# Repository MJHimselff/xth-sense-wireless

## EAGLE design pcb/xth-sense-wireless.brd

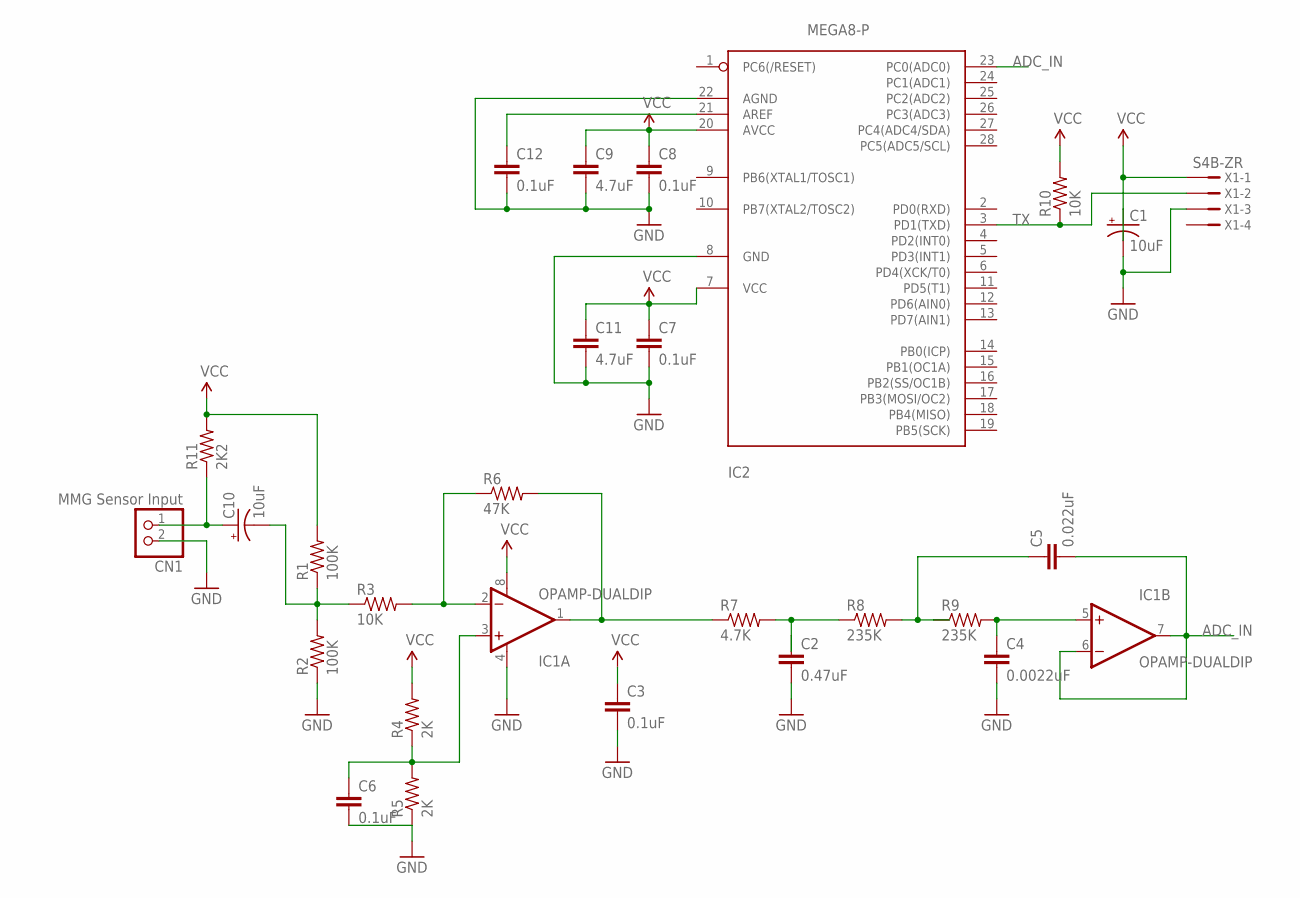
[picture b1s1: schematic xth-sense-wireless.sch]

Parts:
C1, C10: 10uF; CPOL-RADIAL-10UF-25V
C2: 0.47uF; CAP-PTH-SMALL
C3, C6, C7, C8, C12: 0.1uF; CAP-PTH-SMALL
C4: 0.0022uF; CAP-PTH-SMALL
C5: 0.022uF; CAP-PTH-SMALL
C9, C11: 4.7uF; CAP-PTH-SMALL
CN1: MMG Sensor Input; JST-PH-2-THM-RA
IC1: OPAMP-DUALDIP; DIP08
IC2: MEGA8-P; DIL28-3
R1, R2: 100K; AXIAL-0.3
R3, R10: 10K; AXIAL-0.3
R4, R5: 2K; AXIAL-0.3
R6: 47K; AXIAL-0.3
R7: 4.7K; AXIAL-0.3
R8, R9: 235K; AXIAL-0.3
R11: 2K2; AXIAL-0.3
X1: S4B-ZR

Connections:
ADC_IN: C5.2, IC1.6 (-IN), IC1.7 (OUT), IC2.23 (PC0(ADC0))
GND: C1.2 (-), C2.2, C3.2, C4.2, C6.2, C7.2, C8.2, C9.2, C11.2, C12.2, CN1.2 (1), IC1.4 (V-), IC2.8 (GND), IC2.22 (AGND), R2.P$1 (1), R5.P$1 (1), X1.3
unnamed: C10.2 (-), R1.P$1 (1), R2.P$2 (2), R3.P$1 (1)
unnamed: IC1.1 (OUT), R6.P$2 (2), R7.P$1 (1)
unnamed: IC1.2 (-IN), R3.P$2 (2), R6.P$1 (1)
unnamed: C2.1, R7.P$2 (2), R8.P$1 (1)
unnamed: C10.1 (+), CN1.1 (2), R11.P$1 (1)
unnamed: C4.1, IC1.5 (+IN), R9.P$2 (2)
unnamed: C5.1, R8.P$2 (2), R9.P$1 (1)
unnamed: C12.1, IC2.21 (AREF)
TX: IC2.3 (PD1(TXD)), R10.P$1 (1), X1.2
VCC: C1.1 (+), C3.1, C7.1, C8.1, C9.1, C11.1, IC1.8 (V+), IC2.7 (VCC), IC2.20 (AVCC), R1.P$2 (2), R4.P$2 (2), R10.P$2 (2), R11.P$2 (2), X1.1
VIRT_GND: C6.1, IC1.3 (+IN), R4.P$1 (1), R5.P$2 (2)

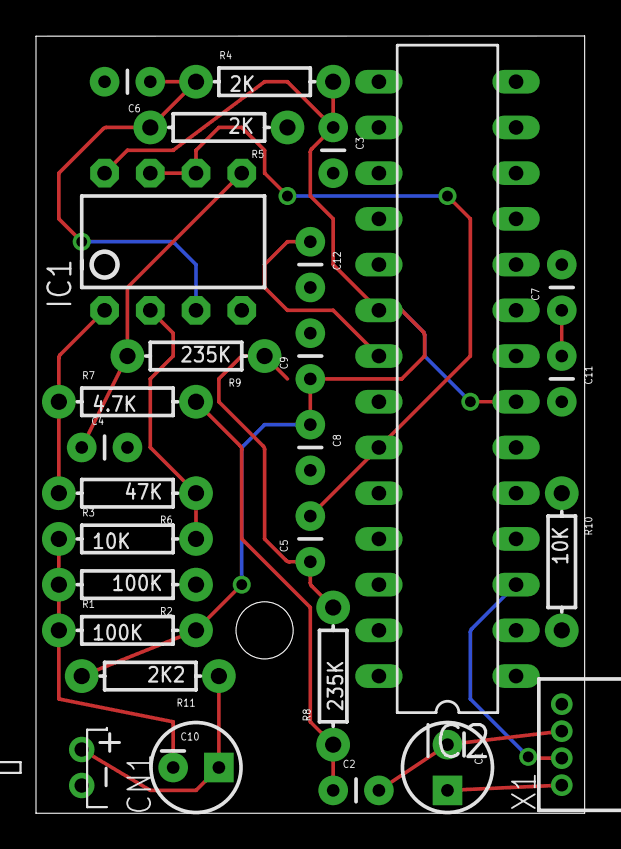
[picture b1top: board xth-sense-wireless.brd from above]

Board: 2 copper layers, 30.5 x 43.2 mm, 27 parts (0 on the bottom side), 13 nets.

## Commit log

2013-02-24 started board layout
2013-02-24 added image of schematic for anti-aliasing filter
2013-02-26 updadted schematic.
2013-02-26 added the avr library for atmega328
2013-02-28 fnished schematic nad board layout (except for ground plane in lower-right corner. put one in for the digital grounds…)

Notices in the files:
parts and their libraries:
SparkFun: Licensing: CC v3.0 Share-Alike You are welcome to use this library for commercial purposes.
